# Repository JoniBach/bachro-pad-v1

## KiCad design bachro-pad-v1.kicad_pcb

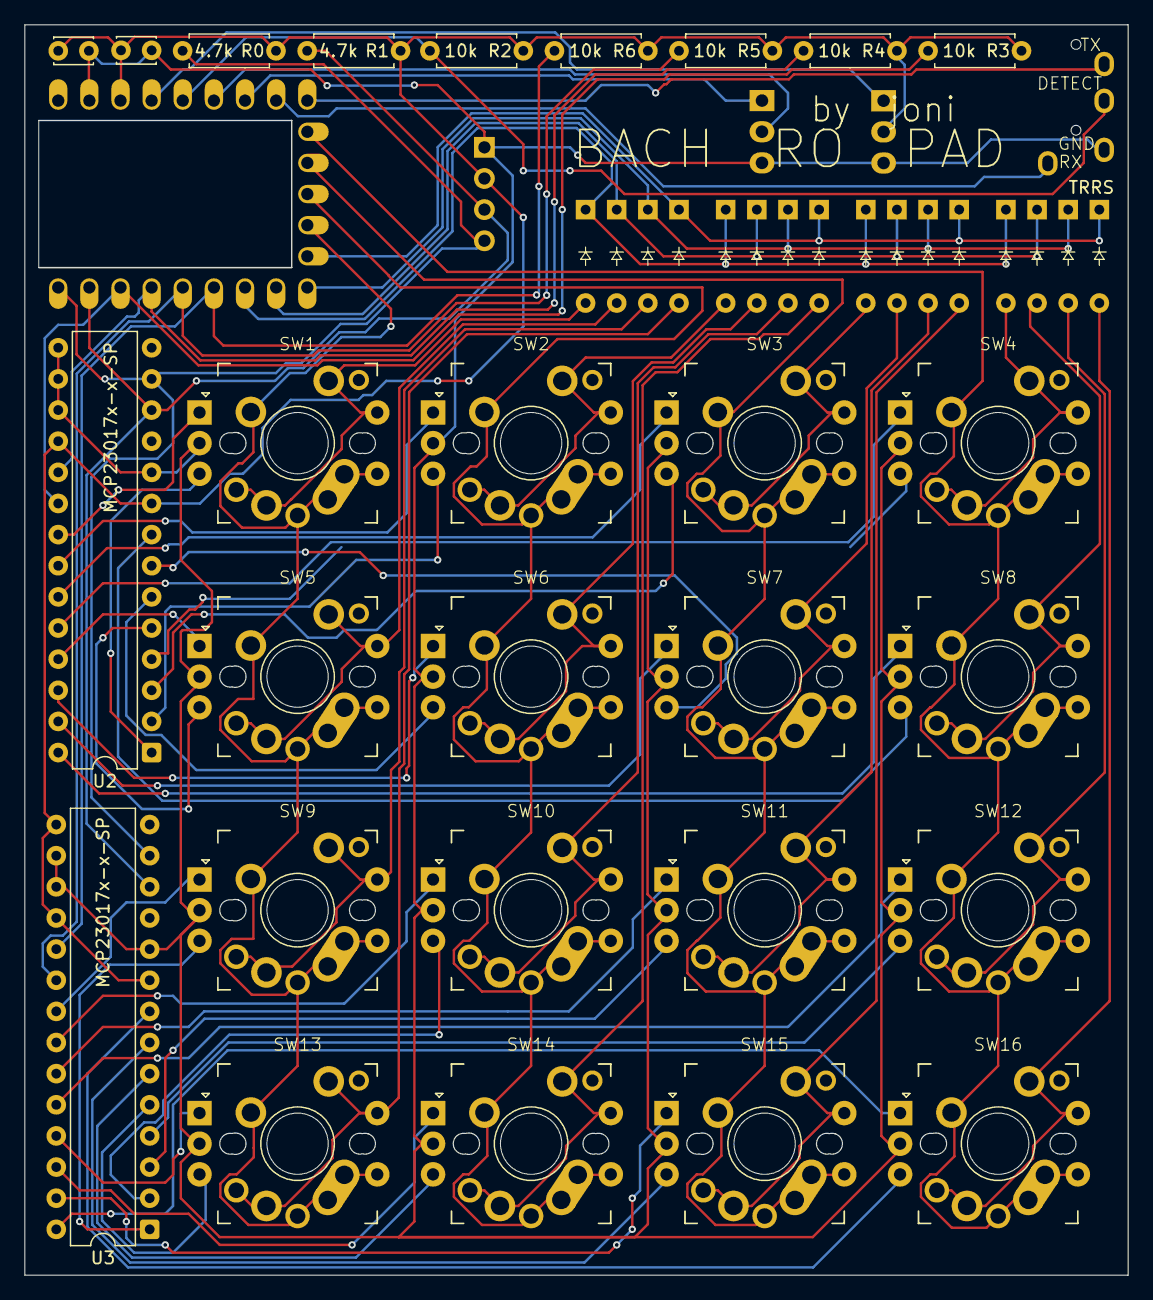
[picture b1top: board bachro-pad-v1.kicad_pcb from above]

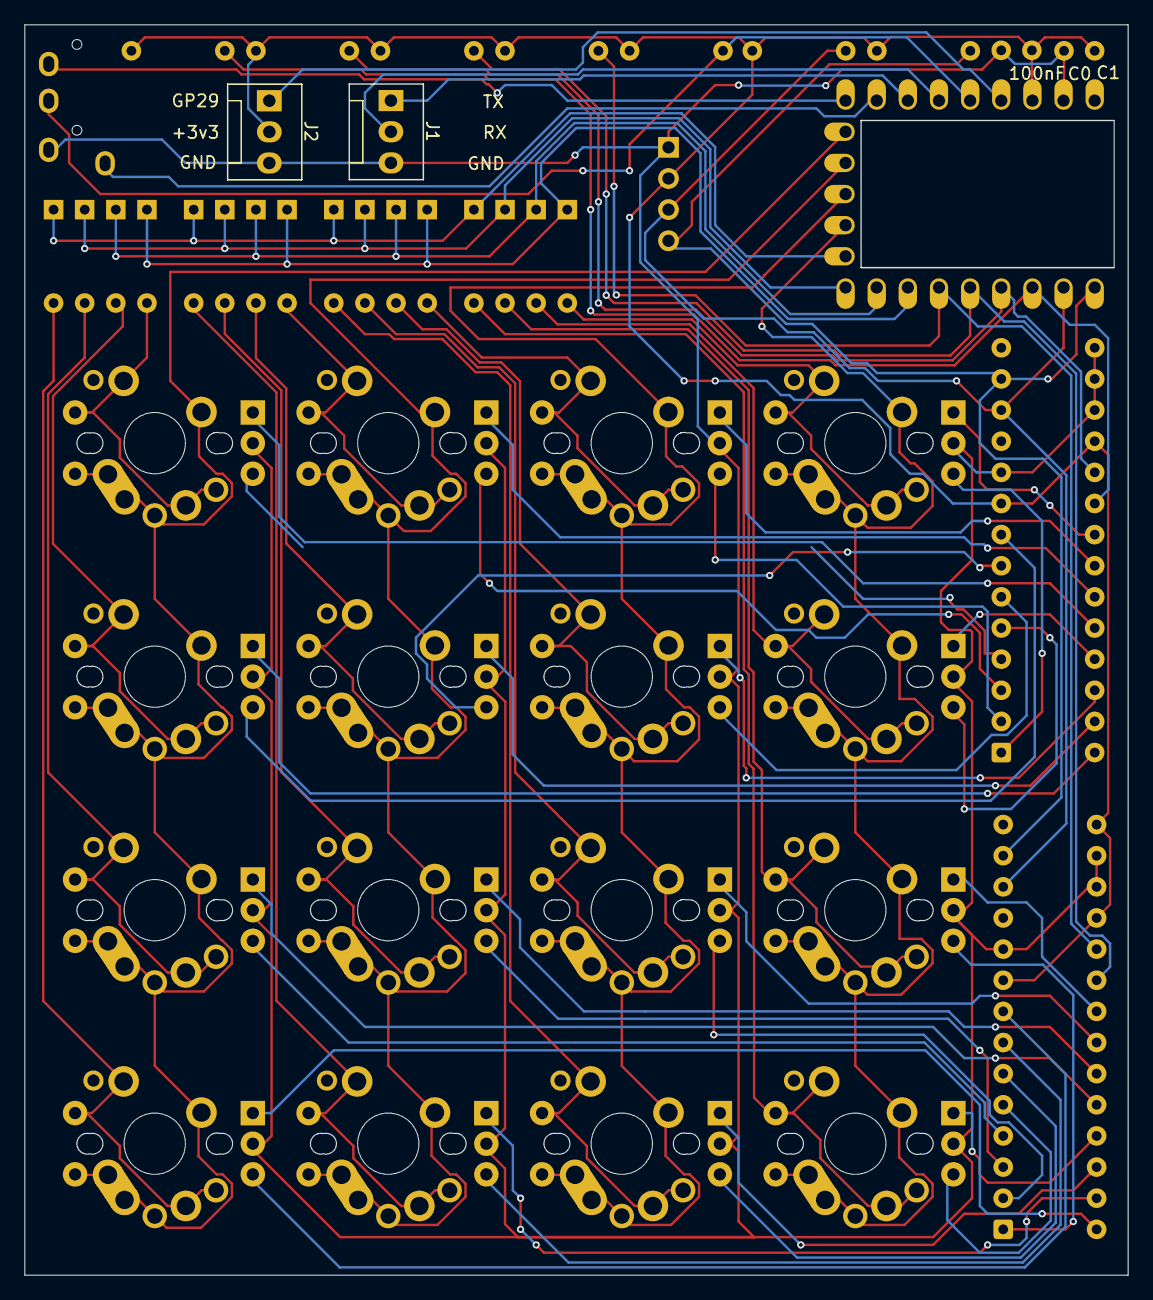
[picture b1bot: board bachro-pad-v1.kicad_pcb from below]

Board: 2 copper layers, 90.0 x 102.0 mm, 48 parts (3 on the bottom side), 70 nets.

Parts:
C0, C1: 100nF; C_Disc_D3.0mm_W2.0mm_P2.50mm
D1, D2, D3, D4, D5, D6, D7, D8, D9, D10, D11, D12, D13, D14, D15, D16: Diode_DO-35
J0: OLED_128x32
J1, J2: Conn_01x03; FanPinHeader_1x03_P2.54mm_Vertical
R0, R1: 4.7k; R_Axial_DIN0207_L6.3mm_D2.5mm_P7.62mm_Horizontal
R2, R3, R4, R5, R6: 10k; R_Axial_DIN0207_L6.3mm_D2.5mm_P7.62mm_Horizontal
SW1, SW2, SW3, SW4, SW5, SW6, SW7, SW8, SW9, SW10, SW11, SW12, SW13, SW14, SW15, SW16: RotaryEncoder_Switch; Choc_V2_hybrid_flex_RotaryEncoder_Alps_EC11E-Switch_Vertica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
U1: rp2040-zero; rp2040-zero-tht
U2, U3: MCP23017x-x-SP; DIP-28_W7.62mm
U4: TRRS; TRRS_PJ-320A

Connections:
+3V3: C0.2, C1.1, J0.2 (VCC), J2.2, R0.2, R1.2, R2.1, R3.1, R4.1, R5.1, R6.1, U1.21 (3V3), U2.9 (V_{DD}), U2.18 (~RESET), U3.9 (V_{DD}), U3.15 (A0), U3.18 (~RESET)
A SW1: SW1.A, U2.21 (GPA0)
A SW2: SW2.A, U2.22 (GPA1)
A SW3: SW3.A, U2.23 (GPA2)
A SW4: SW4.A, U2.24 (GPA3)
A SW5: SW5.A, U2.25 (GPA4)
A SW6: SW6.A, U2.26 (GPA5)
A SW7: SW7.A, U2.27 (GPA6)
A SW8: SW8.A, U2.28 (GPA7)
A SW9: SW9.A, U3.21 (GPA0)
A SW10: SW10.A, U3.22 (GPA1)
A SW11: SW11.A, U3.23 (GPA2)
A SW12: SW12.A, U3.24 (GPA3)
A SW13: SW13.A, U3.25 (GPA4)
A SW14: SW14.A, U3.26 (GPA5)
A SW15: SW15.A, U3.27 (GPA6)
A SW16: SW16.A, U3.28 (GPA7)
B SW1: SW1.B, U2.1 (GPB0)
B SW2: SW2.B, U2.2 (GPB1)
B SW3: SW3.B, U2.3 (GPB2)
B SW4: SW4.B, U2.4 (GPB3)
B SW5: SW5.B, U2.5 (GPB4)
B SW6: SW6.B, U2.6 (GPB5)
B SW7: SW7.B, U2.7 (GPB6)
B SW8: SW8.B, U2.8 (GPB7)
B SW9: SW9.B, U3.1 (GPB0)
B SW10: SW10.B, U3.2 (GPB1)
B SW11: SW11.B, U3.3 (GPB2)
B SW12: SW12.B, U3.4 (GPB3)
B SW13: SW13.B, U3.5 (GPB4)
B SW14: SW14.B, U3.6 (GPB5)
B SW15: SW15.B, U3.7 (GPB6)
B SW16: SW16.B, U3.8 (GPB7)
DEBUG_RX: J1.2, U1.18 (27)
DEBUG_TX: J1.1, U1.17 (26)
unnamed: D1.2 (A), SW1.S2
unnamed: D2.2 (A), SW2.S2
unnamed: D3.2 (A), SW3.S2
unnamed: D4.2 (A), SW4.S2
unnamed: D5.2 (A), SW5.S2
unnamed: D6.2 (A), SW6.S2
unnamed: D7.2 (A), SW7.S2
unnamed: D8.2 (A), SW8.S2
unnamed: D9.2 (A), SW9.S2
unnamed: D10.2 (A), SW10.S2
unnamed: D11.2 (A), SW11.S2
unnamed: D12.2 (A), SW12.S2
unnamed: D13.2 (A), SW13.S2
unnamed: D14.2 (A), SW14.S2
unnamed: D15.2 (A), SW15.S2
unnamed: D16.2 (A), SW16.S2
SCL: J0.3 (SCL), R1.1, U1.2 (1), U2.12 (SCK), U3.12 (SCK)
SDA: J0.4 (SDA), R0.1, U1.1 (0), U2.13 (SDA), U3.13 (SDA)
SPARE_ADC: J2.1, U1.20 (29)
SPLIT_RX: U1.16 (15), U4.1 (SLEEVE)
SPLIT_TX: U1.15 (14), U4.4 (RING2)
TETHER_DETECT: R2.2, U1.19 (28), U4.3 (RING1)
U2 INTA: R3.2, U1.3 (2), U2.20 (INTA)
U2 INTB: R4.2, U1.4 (3), U2.19 (INTB)
U3 INTA: R5.2, U1.5 (4), U3.20 (INTA)
U3 INTB: R6.2, U1.6 (5), U3.19 (INTB)
col 1: SW1.S1, SW5.S1, SW9.S1, SW13.S1, U1.11 (10)
col 2: SW2.S1, SW6.S1, SW10.S1, SW14.S1, U1.12 (11)
col 3: SW3.S1, SW7.S1, SW11.S1, SW15.S1, U1.13 (12)
col 4: SW4.S1, SW8.S1, SW12.S1, SW16.S1, U1.14 (13)
gnd: C0.1, C1.2, J0.1 (GND), J1.3, J2.3, SW1.C, SW2.C, SW3.C, SW4.C, SW5.C, SW6.C, SW7.C, SW8.C, SW9.C, SW10.C, SW11.C, SW12.C, SW13.C, SW14.C, SW15.C, SW16.C, U1.22 (GND), U2.10 (V_{SS}), U2.15 (A0), U2.16 (A1), U2.17 (A2), U3.10 (V_{SS}), U3.16 (A1), U3.17 (A2), U4.2 (TIP)
row 1: D1.1 (K), D2.1 (K), D3.1 (K), D4.1 (K), U1.7 (6)
row 2: D5.1 (K), D6.1 (K), D7.1 (K), D8.1 (K), U1.8 (7)
row 3: D9.1 (K), D10.1 (K), D11.1 (K), D12.1 (K), U1.9 (8)
row 4: D13.1 (K), D14.1 (K), D15.1 (K), D16.1 (K), U1.10 (9)

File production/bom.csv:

Designator,Footprint,Quantity,Value,LCSC Part #
"C0, C1",C_Disc_D3.0mm_W2.0mm_P2.50mm,2,100nF,
"D1, D10, D11, D12, D13, D14, D15, D16, D2, D3, D4, D5, D6, D7, D8, D9",Diode_DO-35,16,~,
J0,OLED_128x32,1,OLED_128x32,
"J1, J2",FanPinHeader_1x03_P2.54mm_Vertical,2,Conn_01x03,
"R0, R1",R_Axial_DIN0207_L6.3mm_D2.5mm_P7.62mm_Horizontal,2,4.7k,
"R2, R3, R4, R5, R6",R_Axial_DIN0207_L6.3mm_D2.5mm_P7.62mm_Horizontal,5,10k,
"SW1, SW10, SW11, SW12, SW13, SW14, SW15, SW16, SW2, SW3, SW4, SW5, SW6, SW7, SW8, SW9",Choc_V2_hybrid_flex_RotaryEncoder_Alps_EC11E-Switch_Vertical_H20mm,16,RotaryEncoder_Switch,
U1,rp2040-zero-tht,1,rp2040-zero,
"U2, U3",DIP-28_W7.62mm,2,MCP23017x-x-SP,
U4,TRRS_PJ-320A,1,TRRS,
